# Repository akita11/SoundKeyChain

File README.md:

# SoundKeyChain

最大3つの音声ファイル（MP3形式）を保存し、ボタンを押して再生します。
お気に入りの音声データをいつも持ち運んで再生できます。。

## 使い方

コイン電池(CR2025 or CR2032)を、基板側がマイナス側に向きに差し込みます。

1, 2, 3のボタンを押すと、それぞれ001.mpg, 002.mp3, 003.mp3を再生します。

※音声再生中の消費電流が約10mA程度で、再生終了の約2秒後に低消費電力モード（5uA程度）になります。

[音声再生例](https://github.com/user-attachments/assets/13cc77fd-8777-434c-830f-a518a013cece)

## 音声データの保存

**コイン電池をはずし**、USB Type-CケーブルでPCと接続すると、USBメモリドライブとして認識されます。
用意した音声データ（最大3つ、合計約300KB以下）のファイルをコピーし、とりはずしてください。
ファイル名は、各ボタンに応じて"001.mp3", "002.mp3", "003.mp3"としてください（固定）。

容量は合計で最大300KBのため、必要に応じてビットレートやビット数の調整、モノラル化などの処理を行ってください。
（例えば[Webのmp3データ形式変換サイト](https://online-audio-converter.com/ja/)などを利用できます）

## 音量の変更

PCに接続してUSBメモリとして認識されているドライブの中にあるconfig.txtで機能を設定をできます。設定方法の詳細はconfig.txtに記載されていますが、1行目の2-3文字目（初期設定では"30"）で音量を変更できます（最大30）。

## Author

Junichi Akita (@akita11) / akita@ifdl.jp

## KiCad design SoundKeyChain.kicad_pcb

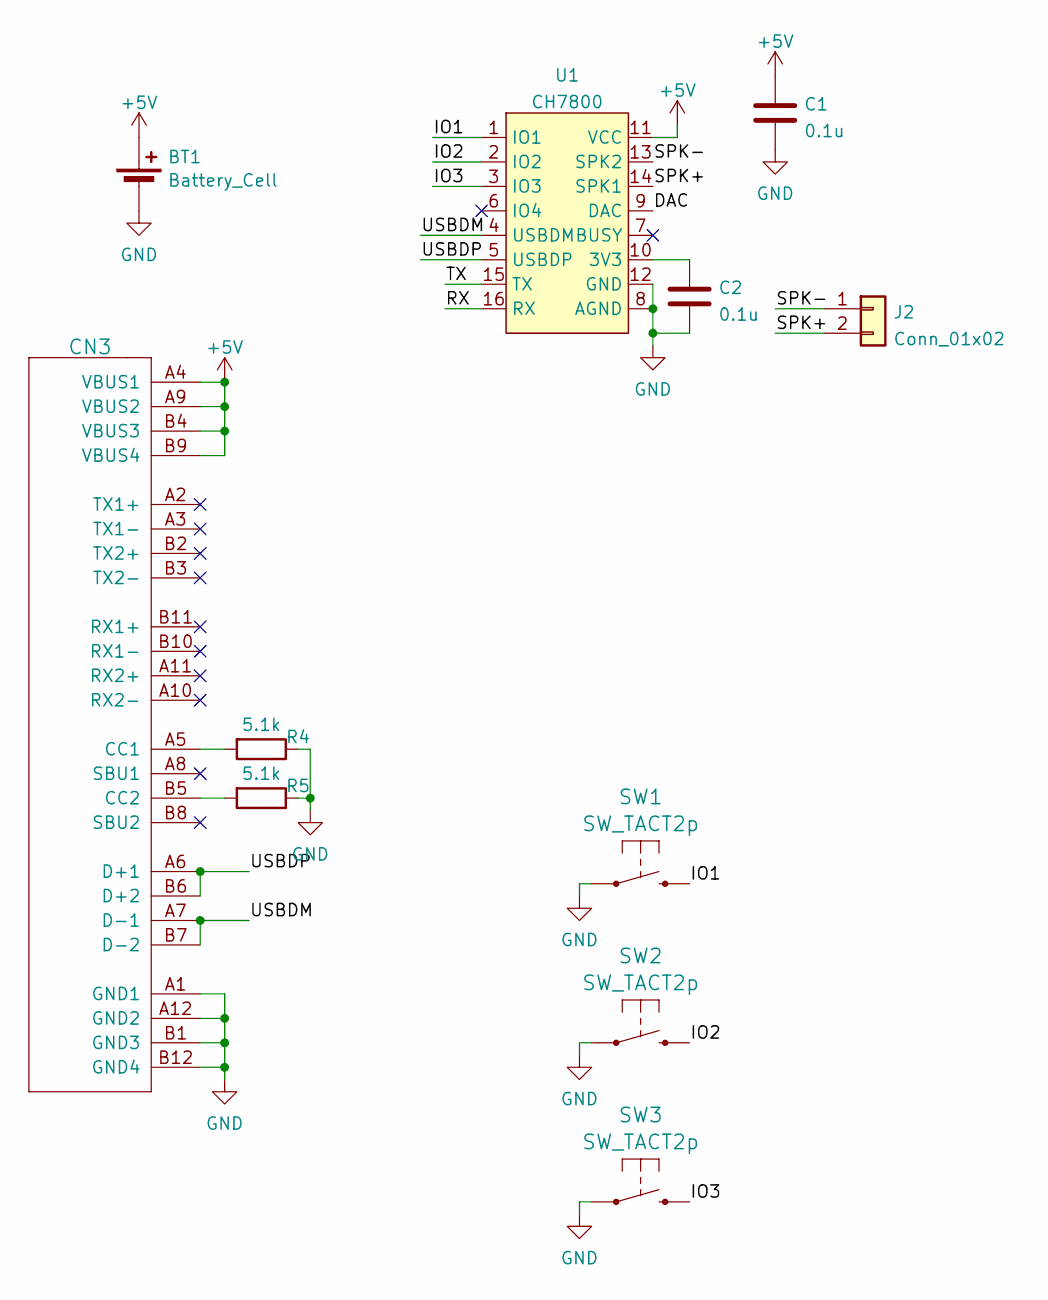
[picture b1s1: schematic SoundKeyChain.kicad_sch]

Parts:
BT1: Battery_Cell; BAT_CR2032_BC-2001
C1, C2: 0.1u; C_0603_1608Metric
CN3: CON_USB-CPCBPLUG; USB-C_PCBPLUG
J2: Conn_01x02; PinHeader_1x02_P2.54mm_Vertical
R4, R5: 5.1k; R_0603_1608Metric
SW1, SW2, SW3: SW_TACT2p; SW_Push_SPST_NO_Alps_SKRK
U1: CH7800; SOP-16_4.4x10.4mm_P1.27mm

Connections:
+5V: BT1.1 (+), C1.1, CN3.A4 (VBUS1), CN3.A9 (VBUS2), CN3.B4 (VBUS3), CN3.B9 (VBUS4), U1.11 (VCC)
/DAC: U1.9 (DAC)
/IO1: SW1.2, U1.1 (IO1)
/IO2: SW2.2, U1.2 (IO2)
/IO3: SW3.2, U1.3 (IO3)
/RX: U1.16 (RX)
/SPK+: J2.2, U1.14 (SPK1)
/SPK-: J2.1, U1.13 (SPK2)
/TX: U1.15 (TX)
/USBDM: CN3.A7 (D-1), CN3.B7 (D-2), U1.4 (USBDM)
/USBDP: CN3.A6 (D+1), CN3.B6 (D+2), U1.5 (USBDP)
GND: BT1.2 (-), C1.2, C2.2, CN3.A1 (GND1), CN3.A12 (GND2), CN3.B1 (GND3), CN3.B12 (GND4), R4.1, R5.1, SW1.1, SW2.1, SW3.1, U1.8 (AGND), U1.12 (GND)
unnamed: CN3.A5 (CC1), R4.2
unnamed: CN3.B5 (CC2), R5.2
unnamed: C2.1, U1.10 (3V3)

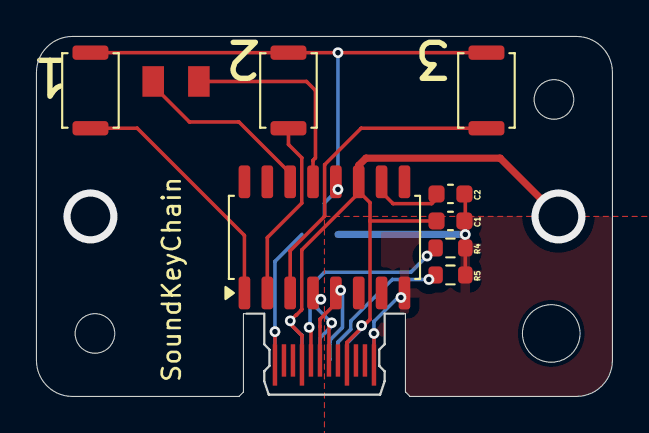
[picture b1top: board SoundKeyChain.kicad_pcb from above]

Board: 2 copper layers, 32.0 x 20.0 mm, 11 parts (1 on the bottom side), 12 nets.
